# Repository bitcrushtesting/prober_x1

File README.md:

# PROBER X1

A hardware tool to help get access to PCB test points, on both sides of the PCB.

## USAGE

## BUILD

## LICENSE

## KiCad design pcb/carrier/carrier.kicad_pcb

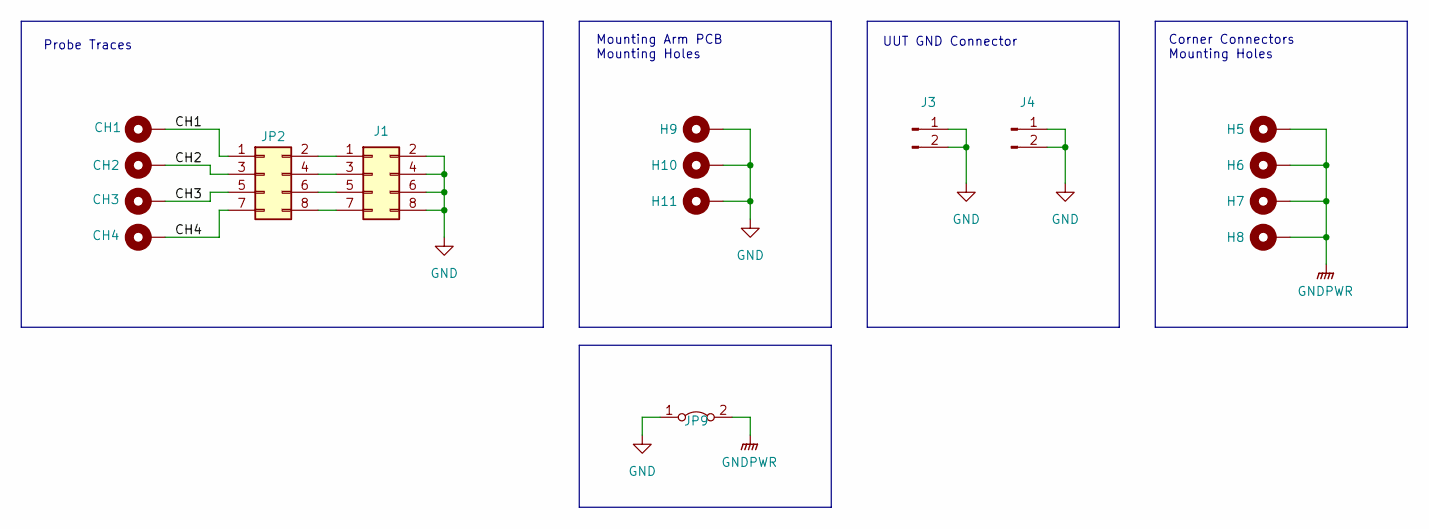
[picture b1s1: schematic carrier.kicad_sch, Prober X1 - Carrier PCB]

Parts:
CH1, CH2, CH3, CH4: MountingHole_Pad; MountingHole_3.2mm_M3_9mm_Pad
H5, H6, H7, H8, H9, H10, H11: MountingHole_Pad; MountingHole_3.2mm_M3_DIN965_Pad
J1: Conn_02x04_Odd_Even; IDC-Header_2x04_P2.54mm_Vertical_SMD
J3, J4: Conn_01x02_Pin; HARWIN_M20-8890245R
JP2: Conn_02x04_Odd_Even; PinHeader_2x04_P2.54mm_Vertical_SMD
JP9: Jumper_2_Bridged; PinHeader_1x02_P2.54mm_Vertical_SMD_Pin1Right

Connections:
/CH1: CH1.1, JP2.1
/CH2: CH2.1, JP2.3
/CH3: CH3.1, JP2.5
/CH4: CH4.1, JP2.7
GND: H9.1, H10.1, H11.1, J1.2, J1.4, J1.6, J1.8, J3.1, J3.2, J4.1, J4.2, JP9.1 (A)
GNDPWR: H5.1, H6.1, H7.1, H8.1, JP9.2 (B)
unnamed: J1.1, JP2.2
unnamed: J1.3, JP2.4
unnamed: J1.5, JP2.6
unnamed: J1.7, JP2.8

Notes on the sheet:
Mounting Arm PCB Mounting Holes
Probe Traces
Corner Connectors Mounting Holes
UUT GND Connector

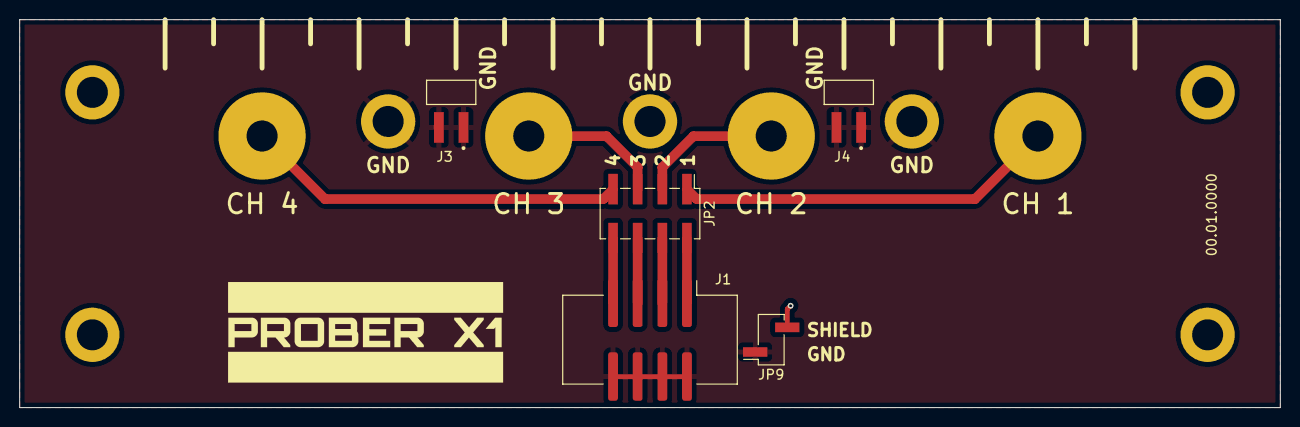
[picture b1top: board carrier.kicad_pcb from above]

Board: 2 copper layers, 130.0 x 40.0 mm, 16 parts (0 on the bottom side), 10 nets.
